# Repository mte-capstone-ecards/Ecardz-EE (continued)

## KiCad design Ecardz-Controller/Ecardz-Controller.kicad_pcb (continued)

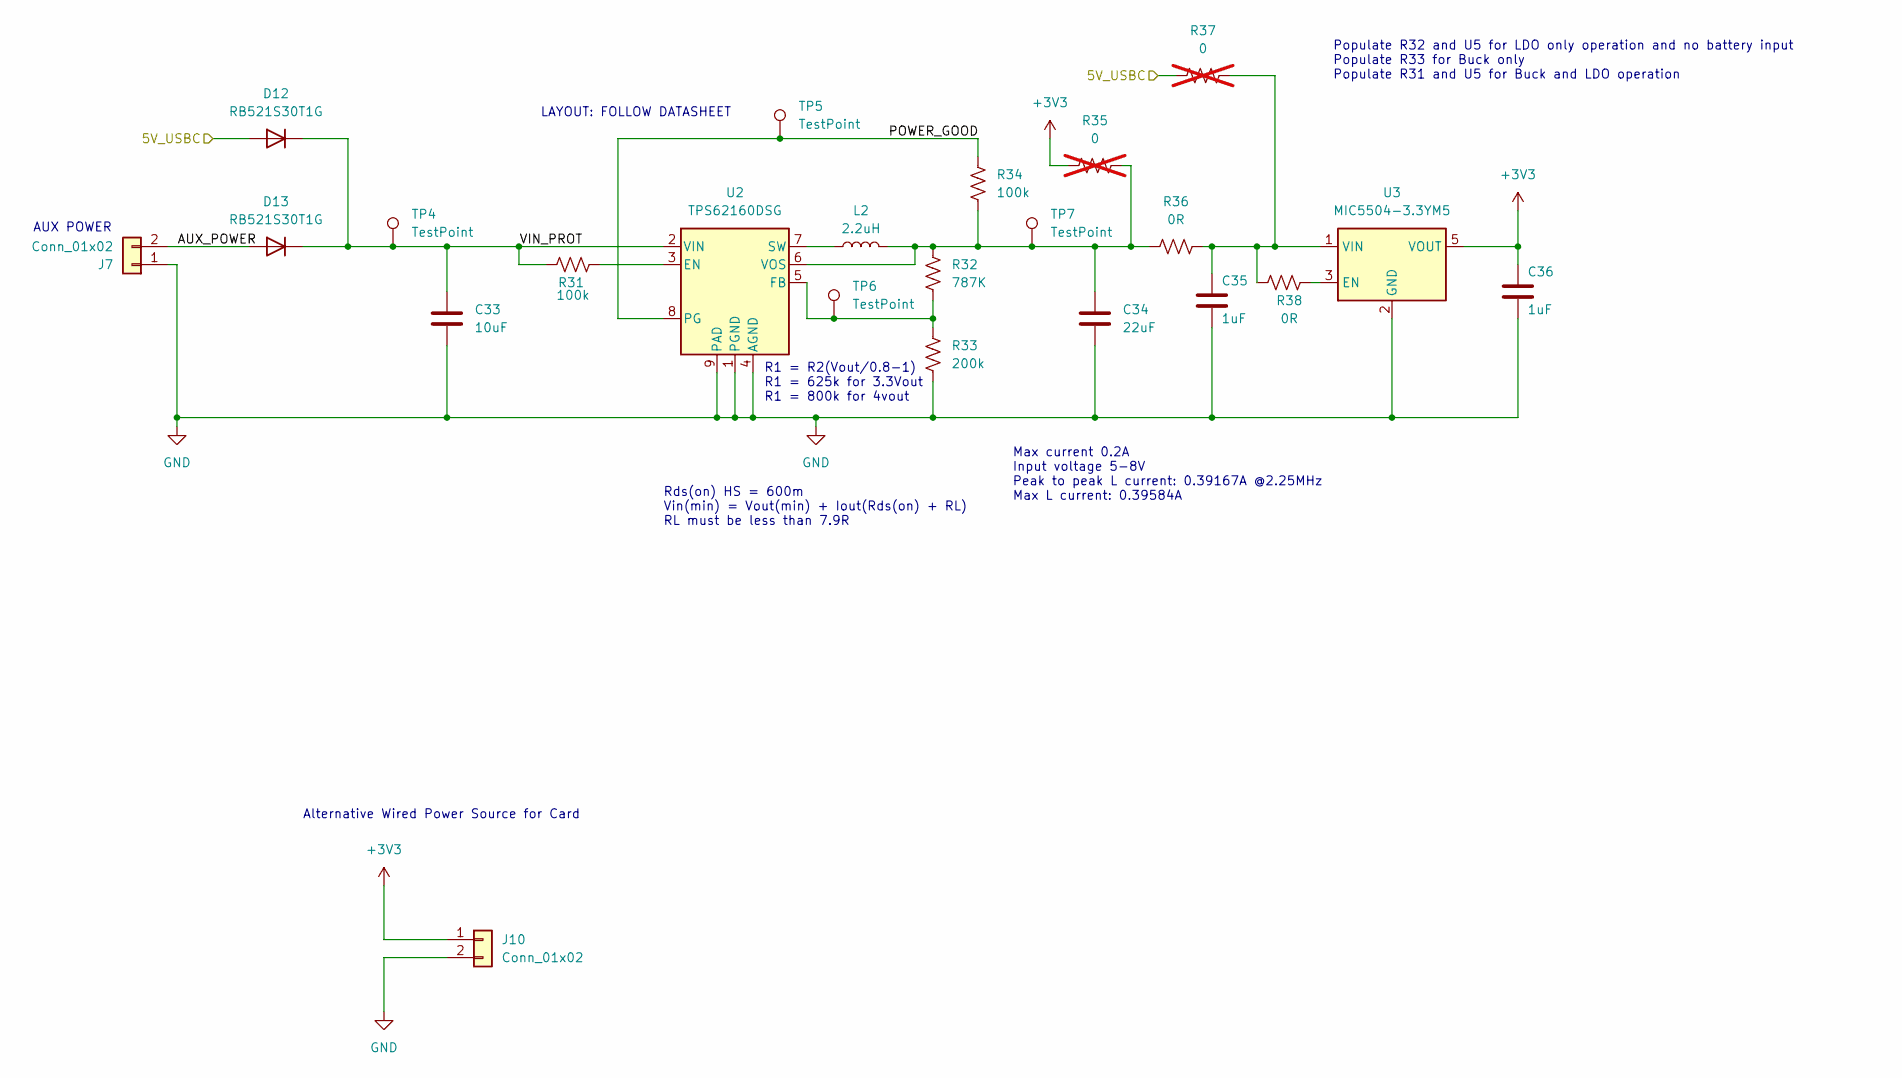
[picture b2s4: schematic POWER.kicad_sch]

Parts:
C33: 10uF; C_0805_2012Metric_Pad1.18x1.45mm_HandSolder; Part Number GRM21BR61C106KE15K
C34: 22uF; C_0805_2012Metric_Pad1.18x1.45mm_HandSolder; Part Number GRM21BR61A226ME51K
C35, C36: 1uF; C_0603_1608Metric_Pad1.08x0.95mm_HandSolder; Part Number CC0603KRX5R8BB105
D12, D13: RB521S30T1G; D_SOD-523; Part Number RB521S30T1G
J7, J10: Conn_01x02; PinHeader_1x02_P2.54mm_Horizontal; Part Number 61300211121
L2: 2.2uH; VLS2016; Part Number VLS201610CX-2R2M-1
R31, R34: 100k; R_0603_1608Metric_Pad0.98x0.95mm_HandSolder; Part Number RC0603FR-07100KL
R32: 787K; R_0603_1608Metric_Pad0.98x0.95mm_HandSolder; Part Number ERJ-3EKF7873V
R33: 200k; R_0603_1608Metric_Pad0.98x0.95mm_HandSolder; Part Number RC0603JR-07200KL
R35, R37: 0; R_0603_1608Metric_Pad0.98x0.95mm_HandSolder; MANUFACTURER PART NUMBER RC0603JR-070RL; Digikey Part Number 311-0.0GRTR-ND; not fitted
R36, R38: 0R; R_0603_1608Metric_Pad0.98x0.95mm_HandSolder; MANUFACTURER PART NUMBER RC0603JR-070RL; Digikey Part Number 311-0.0GRTR-ND
TP4, TP5, TP6, TP7: TestPoint; TestPoint_Pad_D3.0mm
U2: TPS62160DSG; WSON-8-1EP_2x2mm_P0.5mm_EP0.9x1.6mm_ThermalVias; Part Number TPS62160DSG
U3: MIC5504-3.3YM5; SOT-23-5; Part Number MIC5504-3.3YM5-TR

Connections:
+3V3: C36.1, J10.1, R35.1, U3.5 (VOUT); also elsewhere on the board
/POWER/5V_USBC: D12.2 (A), R37.1; also elsewhere on the board
/POWER/AUX_POWER: D13.2 (A), J7.2
/POWER/POWER_GOOD: R34.1, TP5.1, U2.8 (PG)
/POWER/VIN_PROT: C33.1, D12.1 (K), D13.1 (K), R31.2, TP4.1, U2.2 (VIN)
GND: C33.2, C34.2, C35.2, C36.2, J7.1, J10.2, R33.2, U2.1 (PGND), U2.4 (AGND), U2.9 (PAD), U3.2 (GND); also elsewhere on the board
unnamed: R31.1, U2.3 (EN)
unnamed: R32.2, R33.1, TP6.1, U2.5 (FB)
unnamed: L2.1, U2.7 (SW)
unnamed: C34.1, L2.2, R32.1, R34.2, R35.2, R36.1, TP7.1, U2.6 (VOS)
unnamed: R38.1, U3.3 (EN)
unnamed: C35.1, R36.2, R37.2, R38.2, U3.1 (VIN)

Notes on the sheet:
Populate R32 and U5 for LDO only operation and no battery input Populate R33 for Buck only Populate R31 and U5 for Buck and LDO operation
Alternative Wired Power Source for Card
AUX POWER
R1 = R2(Vout/0.8-1) R1 = 625k for 3.3Vout R1 = 800k for 4vout
LAYOUT: FOLLOW DATASHEET
Max current 0.2A Input voltage 5-8V Peak to peak L current: 0.39167A @2.25MHz Max L current: 0.39584A
Rds(on) HS = 600m Vin(min) = Vout(min) + Iout(Rds(on) + RL) RL must be less than 7.9R

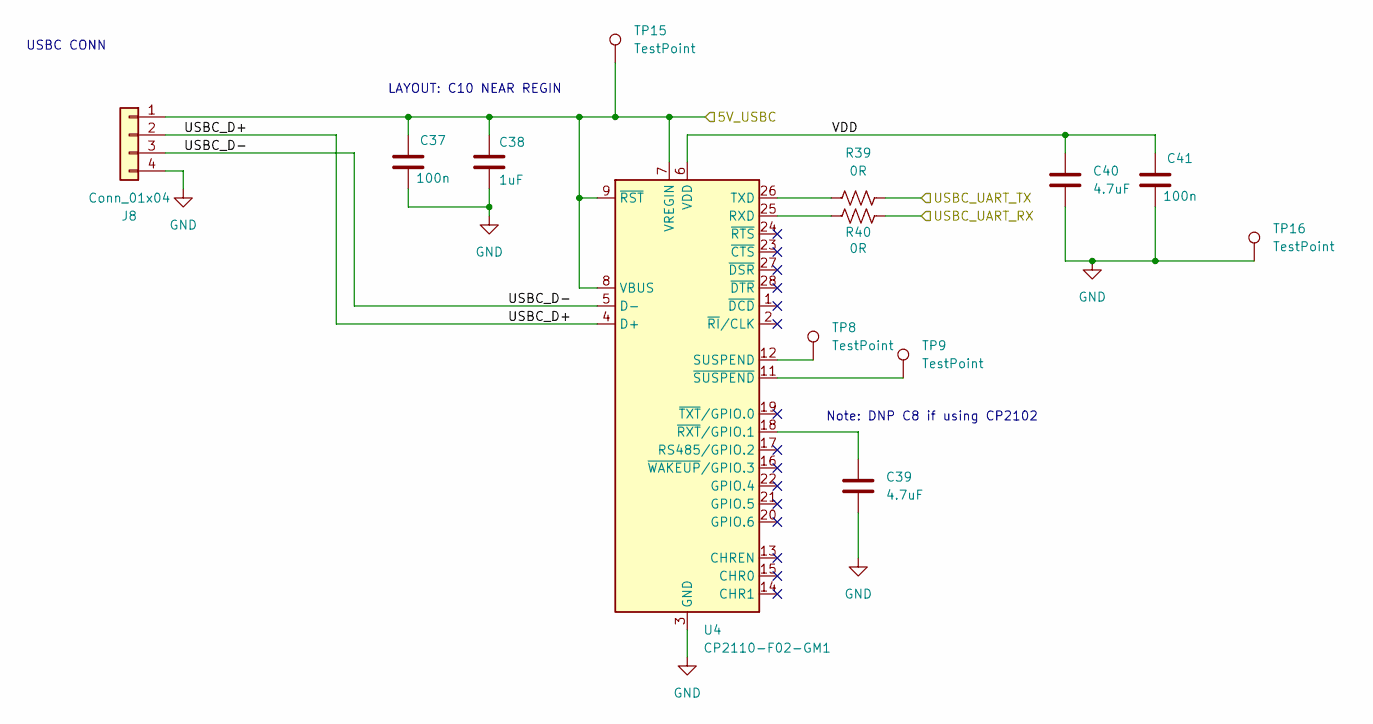
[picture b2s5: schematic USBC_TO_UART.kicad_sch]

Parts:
C37, C41: 100n; C_0603_1608Metric_Pad1.08x0.95mm_HandSolder; Part Number CC0603KRX7R7BB104
C38: 1uF; C_0603_1608Metric_Pad1.08x0.95mm_HandSolder; Part Number CC0603KRX5R8BB105
C39, C40: 4.7uF; C_0603_1608Metric_Pad1.08x0.95mm_HandSolder; Part Number CL10A475KP8NNNC
J8: Conn_01x04; PinHeader_1x04_P2.54mm_Horizontal; Part Number 61300411121
R39, R40: 0R; R_0603_1608Metric_Pad0.98x0.95mm_HandSolder; MANUFACTURER PART NUMBER RC0603JR-070RL; Digikey Part Number 311-0.0GRTR-ND
TP8, TP9, TP15, TP16: TestPoint; TestPoint_Pad_D3.0mm
U4: CP2110-F02-GM1; QFN-28-1EP_5x5mm_P0.5mm_EP3.35x3.35mm; Part Number CP2110-F02-GM1

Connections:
/MCU/USBC_UART_RX: R40.2; also elsewhere on the board
/MCU/USBC_UART_TX: R39.2; also elsewhere on the board
/POWER/5V_USBC: C37.1, C38.1, J8.1, TP15.1, U4.7 (VREGIN), U4.8 (VBUS), U4.9 (~RST); also elsewhere on the board
/USBC_TO_UART/USBC_D+: J8.2, U4.4 (D+)
/USBC_TO_UART/USBC_D-: J8.3, U4.5 (D-)
/USBC_TO_UART/VDD: C40.1, C41.1, U4.6 (VDD)
GND: C37.2, C38.2, C39.2, C40.2, C41.2, J8.4, TP16.1, U4.3 (GND), U4.29 (GND); also elsewhere on the board
unnamed: R40.1, U4.25 (RXD)
unnamed: TP8.1, U4.12 (SUSPEND)
unnamed: R39.1, U4.26 (TXD)
unnamed: C39.1, U4.18 (~RXT/GPIO.1)
unnamed: TP9.1, U4.11 (~SUSPEND)

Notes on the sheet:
USBC CONN
Note: DNP C8 if using CP2102
LAYOUT: C10 NEAR REGIN

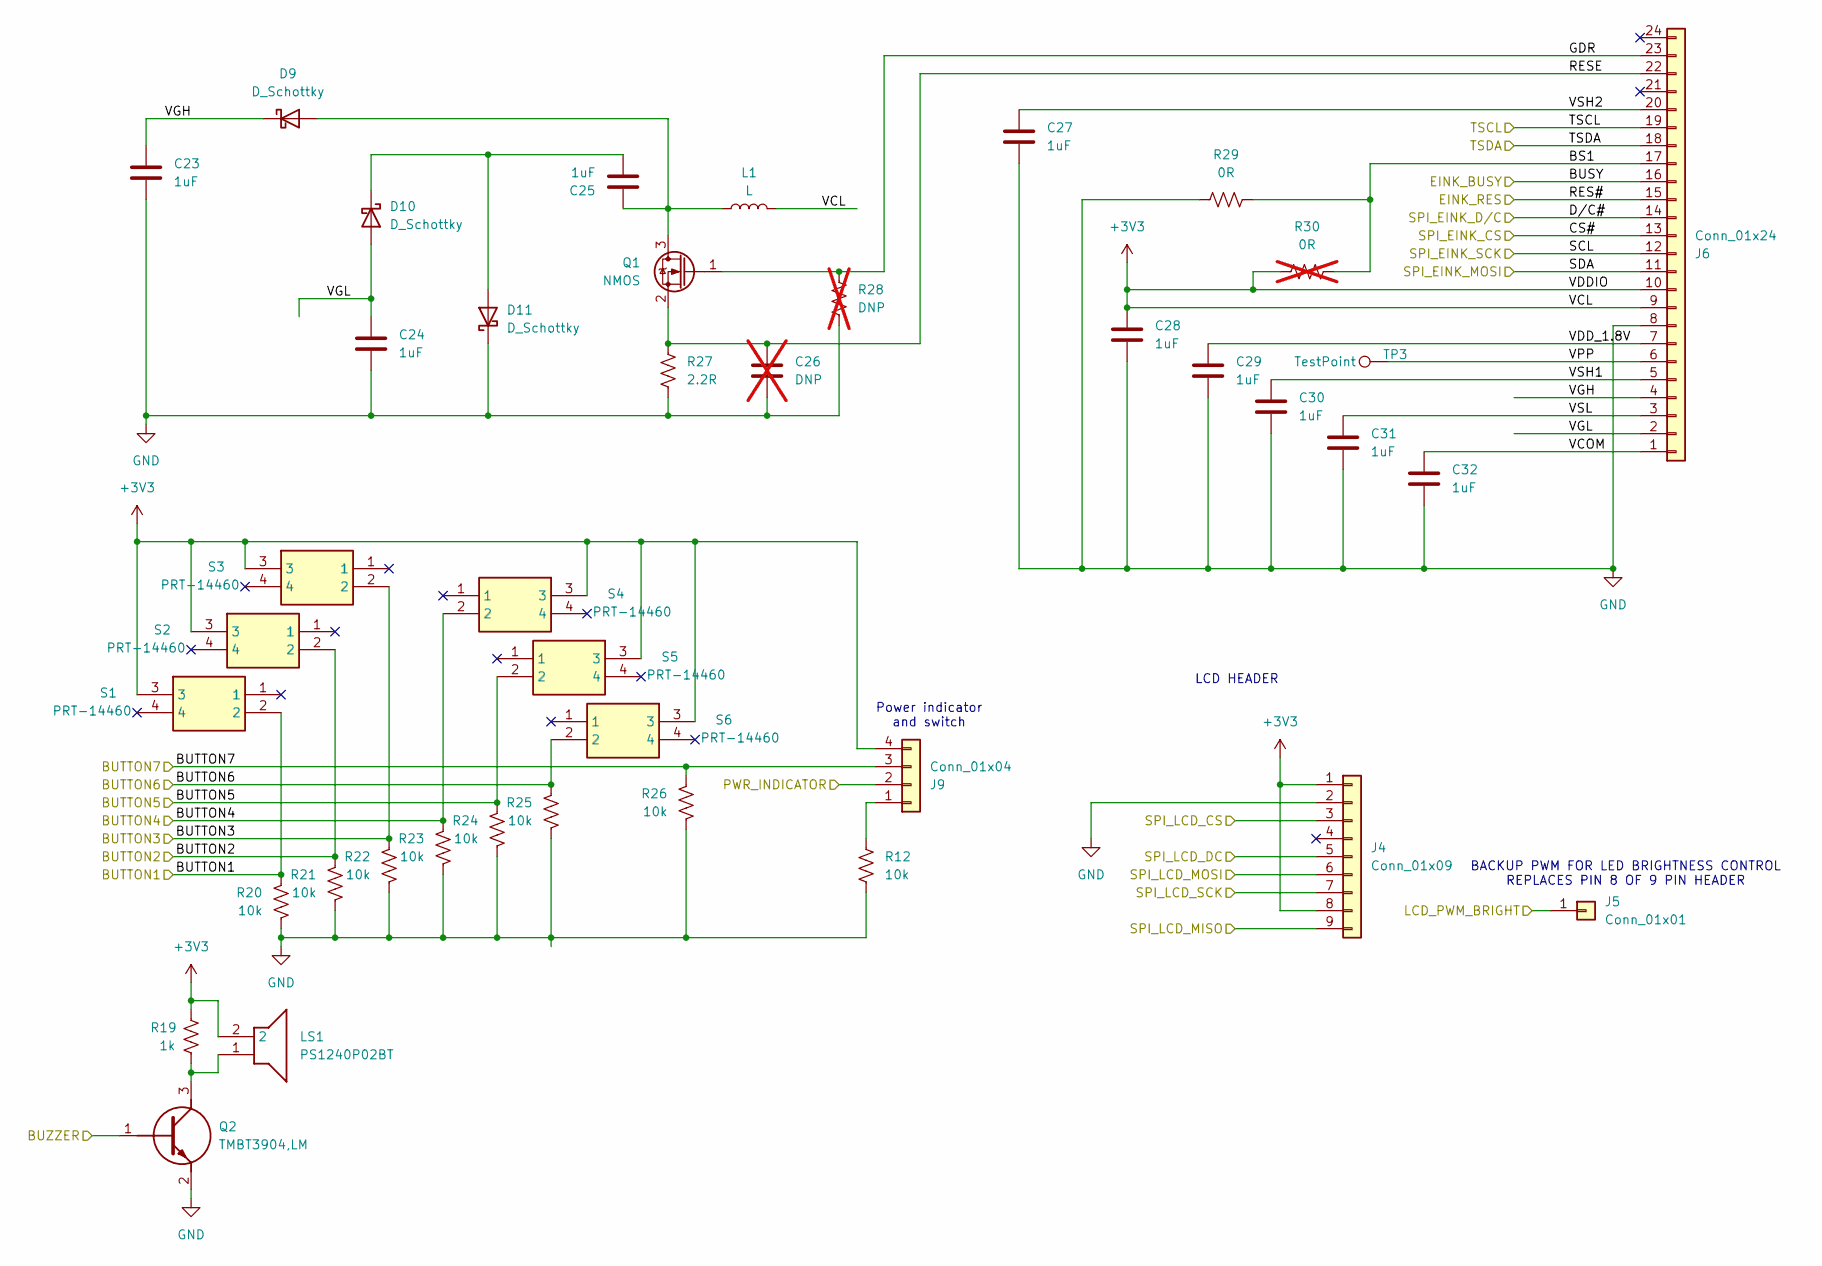
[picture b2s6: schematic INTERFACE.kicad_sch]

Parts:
C23, C24, C25, C27, C28, C29, C30, C31, C32: 1uF; C_0603_1608Metric_Pad1.08x0.95mm_HandSolder; MANUFACTURER PART NUMBER CC0603KRX5R8BB105; Digikey Part Number 311-1445-2-ND
C26: DNP; C_0603_1608Metric_Pad1.08x0.95mm_HandSolder; MANUFACTURER PART NUMBER 100pF; not fitted
D9, D10, D11: D_Schottky; D_SOD-123; MANUFACTURER PART NUMBER MBR0530T1G; Digikey Part Number MBR0530T1GOSTR-ND
J4: Conn_01x09; PinHeader_1x09_P2.54mm_Horizontal; Part Number 61300911121
J5: Conn_01x01; PinHeader_1x01_P2.54mm_Horizontal; Part Number 61300111121
J6: Conn_01x24; TE_2-1734839-4_1x24-1MP_P0.5mm_Horizontal; MANUFACTURER PART NUMBER 10051922-2410ELF
J9: Conn_01x04; PinHeader_1x04_P2.54mm_Horizontal; Part Number 61300411121
L1: L; CDRH5D18; MANUFACTURER PART NUMBER CDRH5D18NP-470NC; Digikey Part Number 308-2060-2-ND
LS1: PS1240P02BT; Mouser Part Number 810-PS1240P02BT
Q1: NMOS; SOT-23; MANUFACTURER PART NUMBER IRLML2803TRPBF; Digikey Part Number IRLML2803PBFTR-ND
Q2: TMBT3904,LM; TMBT3904LM; Mouser Part Number 757-TMBT3904LM
R12, R20, R21, R22, R23, R24, R25, R26: 10k; R_0603_1608Metric_Pad0.98x0.95mm_HandSolder; Part Number RC0603FR-0710KL
R19: 1k; R_0603_1608Metric_Pad0.98x0.95mm_HandSolder; Part Number RC0603FR-071KL
R27: 2.2R; R_0603_1608Metric_Pad0.98x0.95mm_HandSolder; MANUFACTURER PART NUMBER RC0603FR-072R2L; Digikey Part Number 311-2.2HRTR-ND
R28: DNP; R_0603_1608Metric_Pad0.98x0.95mm_HandSolder; MANUFACTURER PART NUMBER 100kR; not fitted
R29: 0R; R_0603_1608Metric_Pad0.98x0.95mm_HandSolder; MANUFACTURER PART NUMBER RC0603JR-070RL; Digikey Part Number 311-0.0GRTR-ND
R30: 0R; R_0603_1608Metric_Pad0.98x0.95mm_HandSolder; MANUFACTURER PART NUMBER RC0603JR-070RL; Digikey Part Number 311-0.0GRTR-ND; not fitted
S1, S2, S3, S4, S5, S6: PRT-14460; PRT14460; Mouser Part Number 474-PRT-14460
TP3: TestPoint; TestPoint_Pad_D3.0mm

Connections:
+3V3: C28.1, J4.1, J4.8, J6.9, J6.10, J9.4, L1.2, LS1.2, R19.1, R30.1, S1.3, S2.3, S3.3, S4.3, S5.3, S6.3; also elsewhere on the board
/INTERFACE/BS1: J6.17, R29.2, R30.2
/INTERFACE/BUSY: J6.16; also elsewhere on the board
/INTERFACE/BUTTON1: R20.1, S1.2; also elsewhere on the board
/INTERFACE/BUTTON2: R21.1, S2.2; also elsewhere on the board
/INTERFACE/BUTTON3: R22.1, S3.2; also elsewhere on the board
/INTERFACE/BUTTON4: R23.1, S4.2; also elsewhere on the board
/INTERFACE/BUTTON5: R24.1, S5.2; also elsewhere on the board
/INTERFACE/BUTTON6: R25.1, S6.2; also elsewhere on the board
/INTERFACE/BUTTON7: J9.3, R26.1; also elsewhere on the board
/INTERFACE/BUZZER: Q2.1 (B); also elsewhere on the board
/INTERFACE/CS#: J6.13; also elsewhere on the board
/INTERFACE/D/C#: J6.14; also elsewhere on the board
/INTERFACE/GDR: J6.23, Q1.1 (G), R28.1
/INTERFACE/LCD_PWM_BRIGHT: J5.1; also elsewhere on the board
/INTERFACE/RES#: J6.15; also elsewhere on the board
/INTERFACE/RESE: C26.1, J6.22, Q1.2 (S), R27.1
/INTERFACE/SCL: J6.12; also elsewhere on the board
/INTERFACE/SDA: J6.11; also elsewhere on the board
/INTERFACE/TSCL: J6.19
/INTERFACE/TSDA: J6.18
/INTERFACE/VCOM: C32.1, J6.1
/INTERFACE/VDD_1.8V: C29.1, J6.7
/INTERFACE/VGH: C23.1, D9.1 (K), J6.4
/INTERFACE/VGL: C24.1, D10.2 (A), J6.2
/INTERFACE/VPP: J6.6, TP3.1
/INTERFACE/VSH1: C30.1, J6.5
/INTERFACE/VSH2: C27.1, J6.20
/INTERFACE/VSL: C31.1, J6.3
/MCU/PWR_INDICATOR: J9.2; also elsewhere on the board
/MCU/SPI_LCD_CS: J4.3; also elsewhere on the board
/MCU/SPI_LCD_DC: J4.5; also elsewhere on the board
/MCU/SPI_LCD_MISO: J4.9; also elsewhere on the board
/MCU/SPI_LCD_MOSI: J4.6; also elsewhere on the board
/MCU/SPI_LCD_SCK: J4.7; also elsewhere on the board
GND: C23.2, C24.2, C26.2, C27.2, C28.2, C29.2, C30.2, C31.2, C32.2, D11.1 (K), J4.2, J6.8, Q2.2 (E), R12.2, R20.2, R21.2, R22.2, R23.2, R24.2, R25.2, R26.2, R27.2, R28.2, R29.1; also elsewhere on the board
unnamed: C25.1, D9.2 (A), L1.1, Q1.3 (D)
unnamed: C25.2, D10.1 (K), D11.2 (A)
unnamed: J9.1, R12.1
unnamed: LS1.1, Q2.3 (C), R19.2

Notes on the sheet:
Power indicator and switch
LCD HEADER
BACKUP PWM FOR LED BRIGHTNESS CONTROL REPLACES PIN 8 OF 9 PIN HEADER

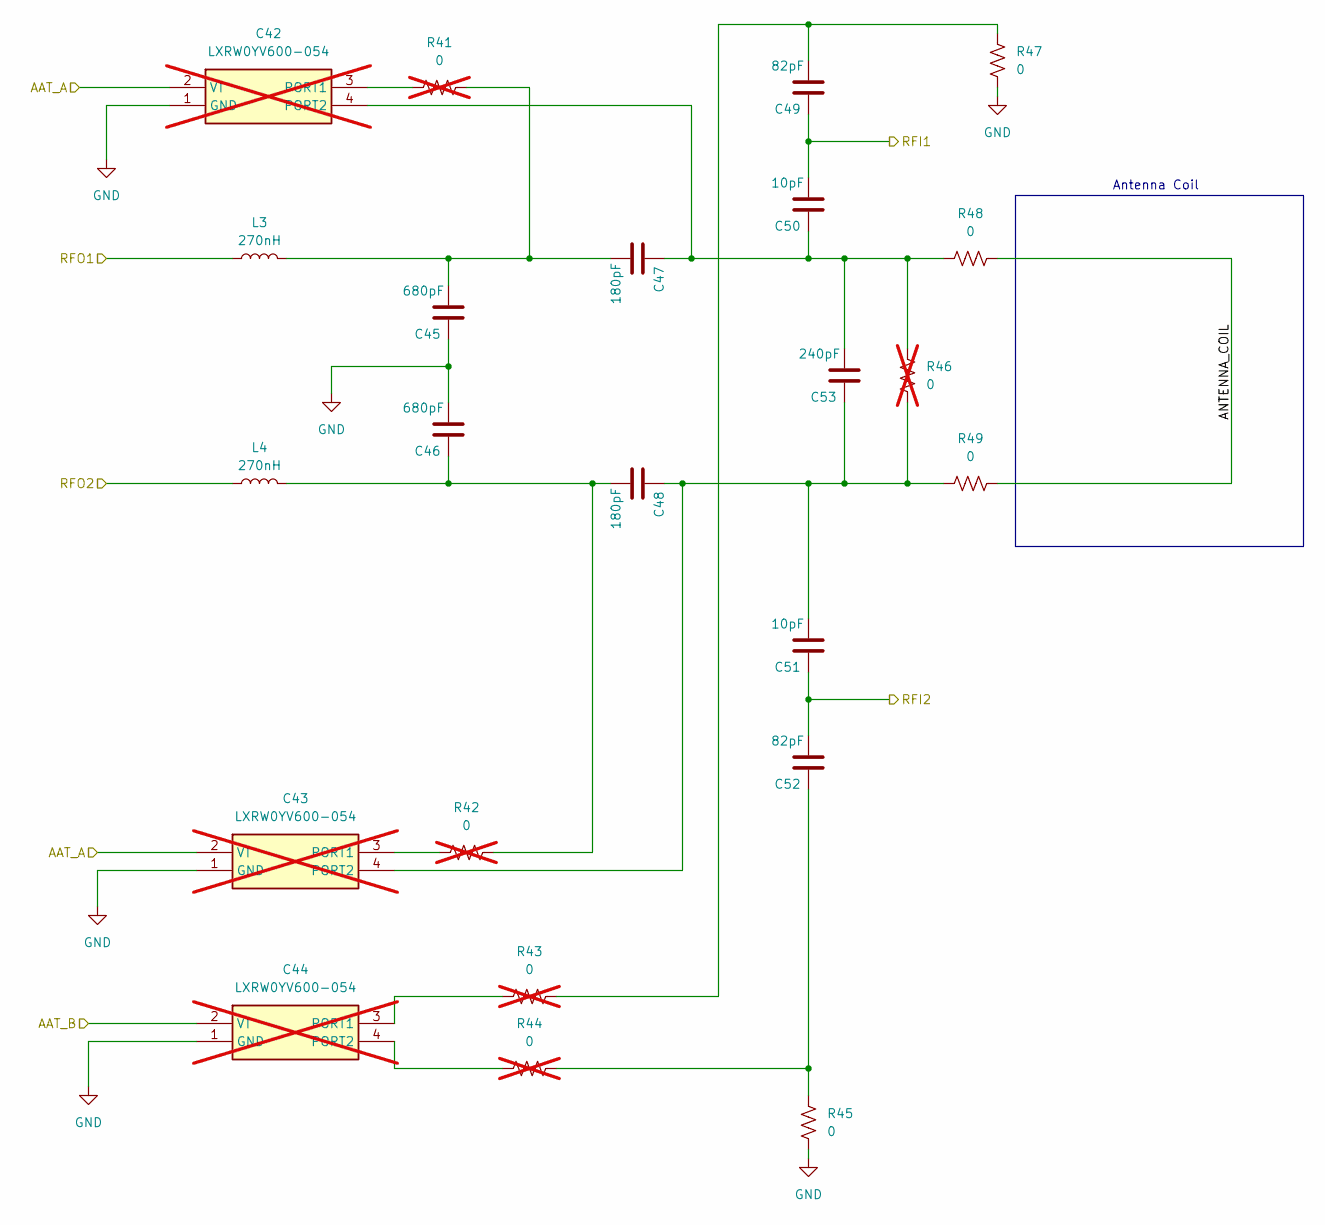
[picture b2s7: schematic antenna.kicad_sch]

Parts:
C42, C43, C44: LXRW0YV600-054; LXRW0YV600054; Mouser Part Number 81-LXRW0YV600-054; not fitted
C45, C46: 680pF; C_0603_1608Metric_Pad1.08x0.95mm_HandSolder; MANUFACTURER PART NUMBER CC0603KRX5R8BB105; Digikey Part Number 311-1445-2-ND
C47, C48: 180pF; C_0603_1608Metric_Pad1.08x0.95mm_HandSolder; MANUFACTURER PART NUMBER CC0603KRX5R8BB105; Digikey Part Number 311-1445-2-ND
C49, C52: 82pF; C_0603_1608Metric_Pad1.08x0.95mm_HandSolder; MANUFACTURER PART NUMBER CC0603KRX5R8BB105; Digikey Part Number 311-1445-2-ND
C50, C51: 10pF; C_0603_1608Metric_Pad1.08x0.95mm_HandSolder; MANUFACTURER PART NUMBER CC0603KRX5R8BB105; Digikey Part Number 311-1445-2-ND
C53: 240pF; C_0603_1608Metric_Pad1.08x0.95mm_HandSolder; MANUFACTURER PART NUMBER CC0603KRX5R8BB105; Digikey Part Number 311-1445-2-ND
L3, L4: 270nH; L_0603_1608Metric; MANUFACTURER PART NUMBER CDRH5D18NP-470NC; Digikey Part Number 308-2060-2-ND
R41, R42, R43, R44, R46: 0; R_0603_1608Metric_Pad0.98x0.95mm_HandSolder; MANUFACTURER PART NUMBER CRCW0603590RFKEA; Digikey Part Number 541-590HTR-ND; not fitted
R45, R47, R48, R49: 0; R_0603_1608Metric_Pad0.98x0.95mm_HandSolder; MANUFACTURER PART NUMBER CRCW0603590RFKEA; Digikey Part Number 541-590HTR-ND

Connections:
/NFC/ANTENNA/AAT_A: C42.2 (VT), C43.2 (VT); also elsewhere on the board
/NFC/ANTENNA/AAT_B: C44.2 (VT); also elsewhere on the board
/NFC/ANTENNA/ANTENNA_COIL: R48.2, R49.2
/NFC/ANTENNA/RFI1: C49.1, C50.2; also elsewhere on the board
/NFC/ANTENNA/RFI2: C51.1, C52.2; also elsewhere on the board
/NFC/ANTENNA/RFO1: L3.1; also elsewhere on the board
/NFC/ANTENNA/RFO2: L4.1; also elsewhere on the board
GND: C42.1 (GND), C43.1 (GND), C44.1 (GND), C45.1, C46.2, R45.2, R47.2; also elsewhere on the board
unnamed: C42.3 (PORT1), R41.1
unnamed: C42.4 (PORT2), C47.1, C50.1, C53.2, R46.2, R48.1
unnamed: C43.3 (PORT1), R42.1
unnamed: C43.4 (PORT2), C48.1, C51.2, C53.1, R46.1, R49.1
unnamed: C44.3 (PORT1), R43.1
unnamed: C44.4 (PORT2), R44.1
unnamed: C45.2, C47.2, L3.2, R41.2
unnamed: C46.1, C48.2, L4.2, R42.2
unnamed: C49.2, R43.2, R47.1
unnamed: C52.1, R44.2, R45.1

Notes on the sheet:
Antenna Coil

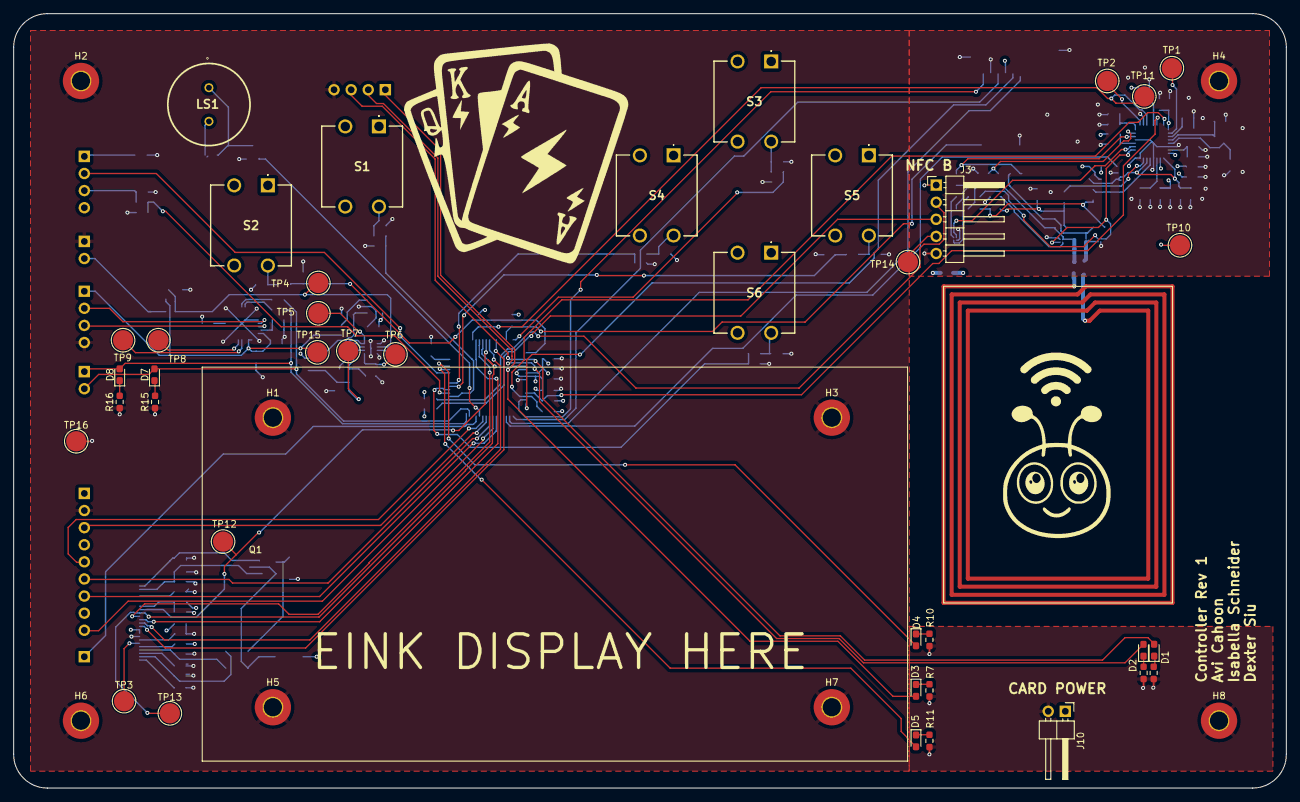
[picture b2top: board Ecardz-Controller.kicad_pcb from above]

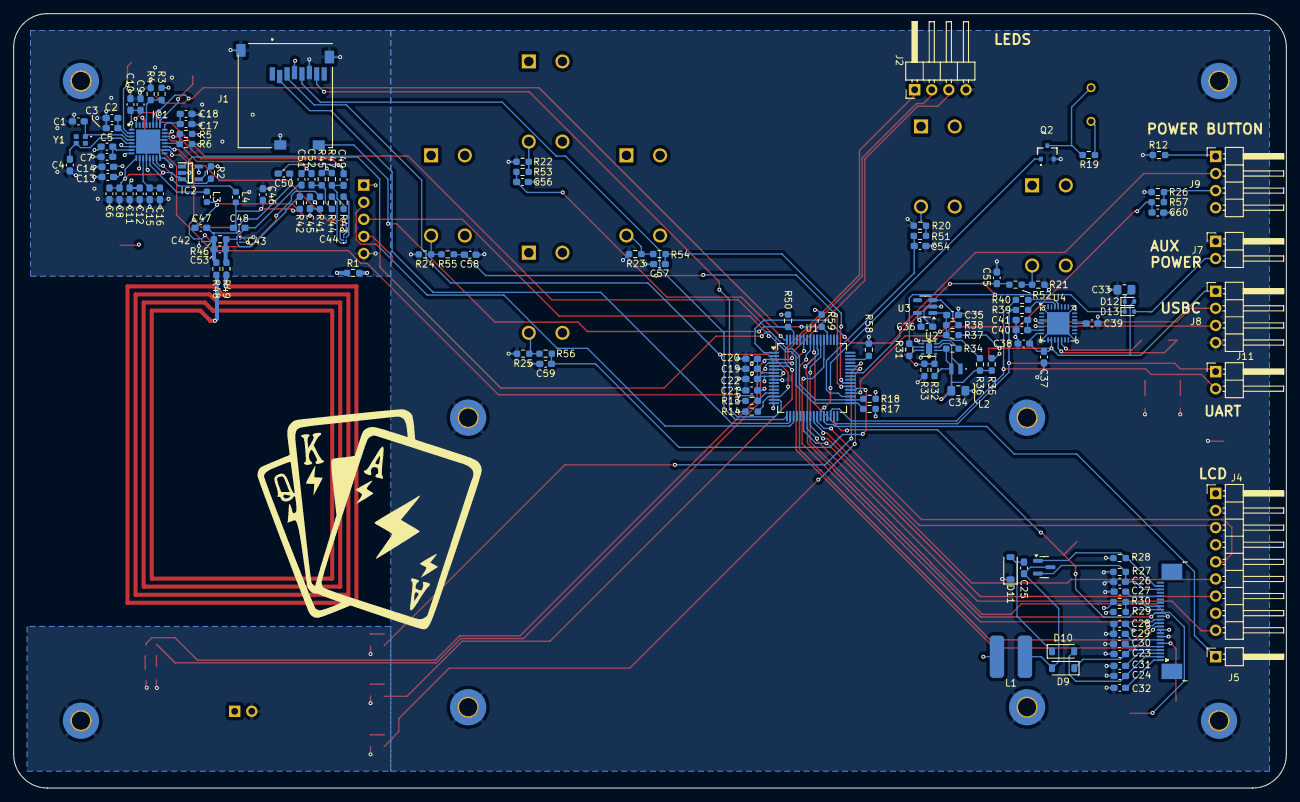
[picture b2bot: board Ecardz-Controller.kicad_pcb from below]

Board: 4 copper layers, 189.0 x 115.0 mm, 186 parts (139 on the bottom side), 119 nets.

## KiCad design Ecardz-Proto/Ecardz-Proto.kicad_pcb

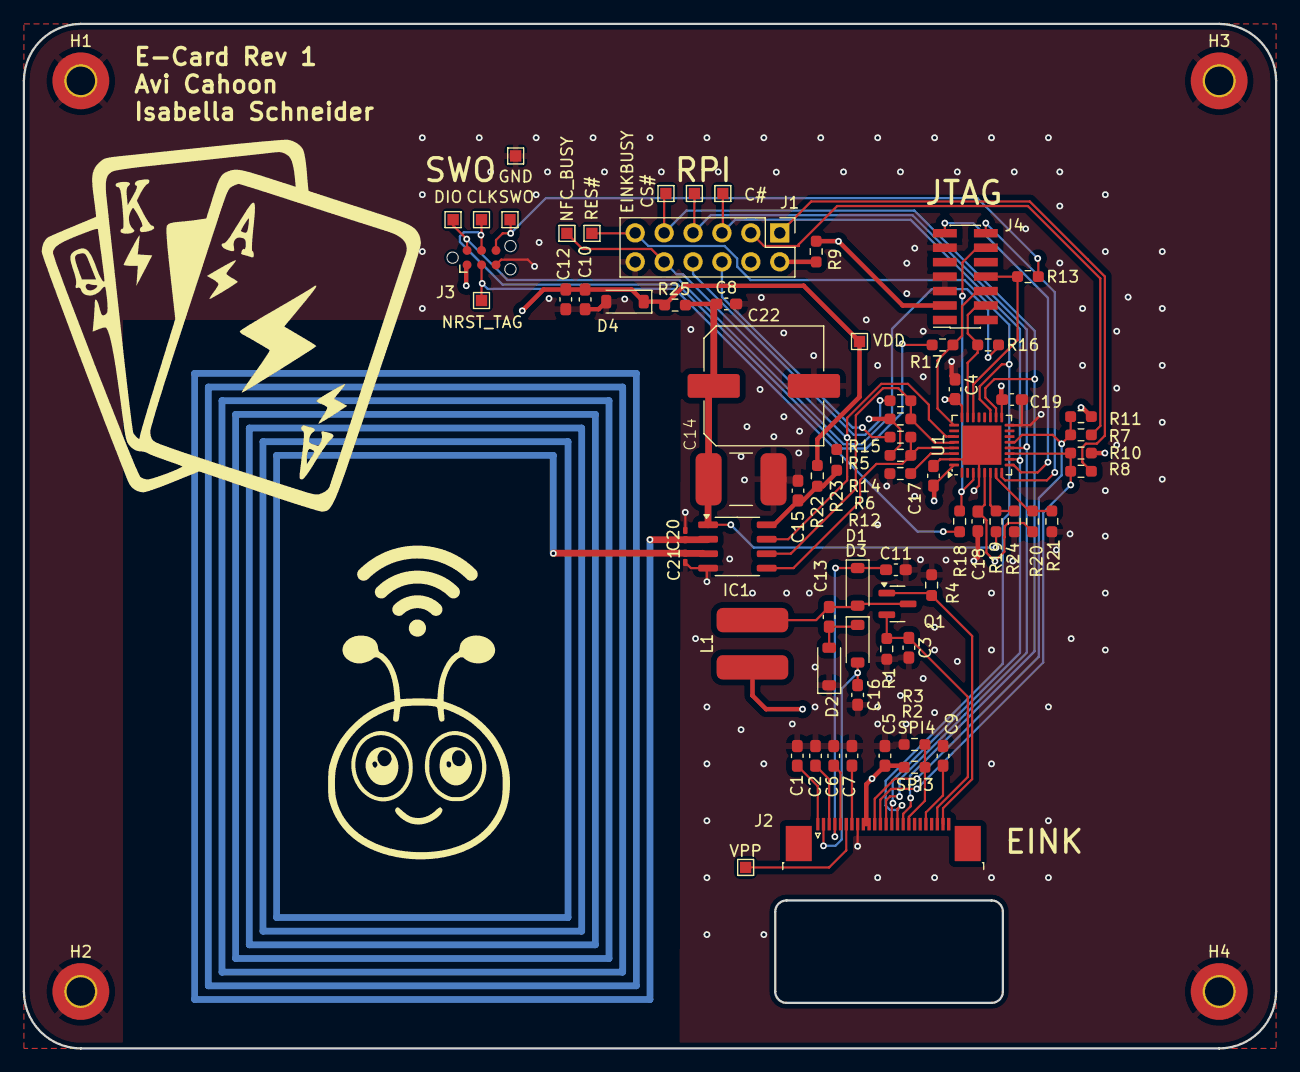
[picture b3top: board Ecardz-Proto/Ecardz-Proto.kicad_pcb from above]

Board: 4 copper layers, 110.0 x 90.0 mm, 75 parts (0 on the bottom side), 45 nets.

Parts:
C1, C2, C4, C5, C6, C7, C9, C11, C13, C16, C17, C18, C19: 1uF; C_0603_1608Metric_Pad1.08x0.95mm_HandSolder
C3: DNP; C_0603_1608Metric_Pad1.08x0.95mm_HandSolder
C8, C10, C12: TBD; C_0603_1608Metric_Pad1.08x0.95mm_HandSolder
C14: TBD; C_2917
C15: 10nF; C_0603_1608Metric_Pad1.08x0.95mm_HandSolder
C20, C21: 7pF; C_0201_0603Metric_Pad0.64x0.40mm_HandSolder
C22: TBD; C_Elec_10x10.2
C#: TestPoint; TestPoint_Pad_1.0x1.0mm
CLK: TestPoint; TestPoint_Pad_1.0x1.0mm
CS#: TestPoint; TestPoint_Pad_1.0x1.0mm
D1, D2, D3: D_Schottky; D_SOD-123
D4: D_Zener; D_SOD-123
DIO: TestPoint; TestPoint_Pad_1.0x1.0mm
EINKBUSY: TestPoint; TestPoint_Pad_1.0x1.0mm
GND: TestPoint; TestPoint_Pad_1.0x1.0mm
H1, H2, H3, H4: MountingHole_Pad; MountingHole_2.5mm_Pad_TopBottom
IC1: M24LR04E-RMN6T/2; SO-8_3.9x4.9mm_P1.27mm
J1: Conn_02x06_Odd_Even; PinHeader_2x06_P2.54mm_Vertical
J2: Conn_01x24; TE_2-1734839-4_1x24-1MP_P0.5mm_Horizontal
J3: Conn_ARM_SWD_TagConnect_TC2030-NL; Tag-Connect_TC2030-IDC-NL_2x03_P1.27mm_Vertical
J4: Conn_02x07_Odd_Even; PinSocket_2x07_P1.27mm_Vertical_SMD
L1: L; CDRH5D18
NFC_BUSY: TestPoint; TestPoint_Pad_1.0x1.0mm
NRST_TAG: TestPoint; TestPoint_Pad_1.0x1.0mm
Q1: NMOS; SOT-23
R1: 2.2R; R_0603_1608Metric_Pad0.98x0.95mm_HandSolder
R2, R3: 0R; R_0603_1608Metric_Pad0.98x0.95mm_HandSolder
R4, R5, R6, R7, R8, R9, R10, R11, R12, R13, R14, R15, R16, R17, R18, R22, R23: DNP; R_0603_1608Metric_Pad0.98x0.95mm_HandSolder
R19, R20, R21, R24: 10k; R_0603_1608Metric_Pad0.98x0.95mm_HandSolder
R25: 600R; R_0603_1608Metric_Pad0.98x0.95mm_HandSolder
RES#: TestPoint; TestPoint_Pad_1.0x1.0mm
SWO: TestPoint; TestPoint_Pad_1.0x1.0mm
U1: STM32L071K8Ux; QFN-32-1EP_5x5mm_P0.5mm_EP3.45x3.45mm
VDD: TestPoint; TestPoint_Pad_1.0x1.0mm
VPP: TestPoint; TestPoint_Pad_1.0x1.0mm

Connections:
+3.3V: J1.2, R9.2
/EINK/BS1: J2.17, R2.2, R3.2
/EINK/BUSY: EINKBUSY.1, J1.9, J2.16, U1.18 (PA8)
/EINK/CS#: CS#.1, J1.7, J2.13, U1.12 (PA6)
/EINK/D/C#: C#.1, J1.5, J2.14, U1.10 (PA4)
/EINK/GDR: J2.23, Q1.1 (G), R4.1
/EINK/RES#: J1.11, J2.15, RES#.1, U1.19 (PA9)
/EINK/RESE: C3.1, J2.22, Q1.2 (S), R1.1
/EINK/SCL: J2.12, R8.2, R10.1, U1.11 (PA5)
/EINK/SDA: J2.11, R7.2, R11.1, U1.13 (PA7)
/EINK/VCOM: C1.1, J2.1
/EINK/VDD_1.8V: C7.1, J2.7
/EINK/VGH: C11.1, D1.1 (K), J2.4
/EINK/VGL: C16.1, D3.2 (A), J2.2
/EINK/VPP: J2.6, VPP.1
/EINK/VSH1: C6.1, J2.5
/EINK/VSH2: C9.1, J2.20
/EINK/VSL: C2.1, J2.3
/NFC/VDD_NFC: C15.1, IC1.8 (VCC), R22.1, R23.1
/NFC/V_E_HARVEST: C8.1, C14.1, C22.1, IC1.1 (VOUT), R19.1, R25.1
/STM/BOOT0: R12.2, U1.30 (BOOT0)
/STM/I2C_NFC_SCL: IC1.6 (SCL), R5.2, R15.2, U1.28 (PB6)
/STM/I2C_NFC_SCL_RPI: J1.8, R15.1
/STM/I2C_NFC_SDA: IC1.5 (SDA), R6.2, R14.2, U1.29 (PB7)
/STM/I2C_NFC_SDA_RPI: J1.6, R14.1
/STM/NFC_BUSY: IC1.7 (RF_WIP/BUSY), J1.10, NFC_BUSY.1, U1.27 (PB5)
/STM/NRST: J4.12, R18.2, U1.3 (NRST)
/STM/NRST_TAG: J3.3 (~RESET), NRST_TAG.1, R18.1
/STM/SPI_EINK_SCL_RPI: J1.1, R10.2
/STM/SPI_EINK_SDA_RPI: J1.3, R11.2
/STM/SWCLK: J4.6, R17.1, U1.25 (PA14)
/STM/SWCLK_TAG: CLK.1, J3.4 (SWCLK), R17.2
/STM/SWDIO: J4.4, R16.1, U1.23 (PA13)
/STM/SWDIO_TAG: DIO.1, J3.2 (SWDIO), R16.2
/STM/SWO: J4.8, R13.1, U1.22 (PA12)
/STM/SWO_TAG: J3.6 (SWO), R13.2, SWO.1
/STM/T_VCP_RX: J4.13, U1.9 (PA3)
/STM/T_VCP_TX: J4.14, U1.8 (PA2)
/STM/VDD_MEAS: R20.2, R21.1, U1.7 (PA1)
GND: C1.2, C2.2, C3.2, C4.1, C5.2, C6.2, C7.2, C8.2, C9.2, C10.2, C11.2, C12.2, C14.2, C15.2, C16.2, C17.1, C18.1, C19.1, C20.2, C21.2, C22.2, D2.1 (K), D4.2 (A), GND.1, H1.1, H2.1, H3.1, H4.1, IC1.4 (VSS), J1.12, J2.8, J3.5 (GND), J4.5, J4.7, J4.11, R1.2, R3.1, R4.2, R12.1, R21.2, R24.2, U1.4 (VSSA), U1.16 (VSS), U1.31 (VSS), U1.33 (VSS)
unnamed: C13.1, D1.2 (A), L1.1, Q1.3 (D)
unnamed: C13.2, D2.2 (A), D3.1 (K)
unnamed: C20.1, C21.1, IC1.2 (AC0), IC1.3 (AC1)
unnamed: R19.2, R24.1, U1.6 (PA0)
VDD: C4.2, C5.1, C10.1, C12.1, C17.2, C18.2, C19.2, D4.1 (K), J2.9, J2.10, J3.1 (VCC), J4.3, L1.2, R2.1, R5.1, R6.1, R7.1, R8.1, R9.1, R20.1, R22.2, R25.2, U1.5 (VDDA), U1.17 (VDD), U1.24 (VDDIO2), U1.32 (VDD), VDD.1

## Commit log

2024-05-08 new project doc
2024-05-08 just kidding we gonna use kicad
2024-06-27 New kicad project
    added kicad project and EINK interface
2024-10-07 added submodule for parts library
2024-10-07 updated parts-lib to newer update
2024-10-07 added EEPROM schematic, removed personal files
2024-10-26 Update .gitmodules
    trying to make it use ssh instead of https
2024-10-26 added energy harvesting schematic page
2024-10-26 upated E-ink schematic
    should be done - just missing inductor footprint
2024-10-29 added energy harvesting sensing ADC to NFC
2024-10-29 updated submodule
2024-11-04 removed eeprom
2024-11-06 added STM and rpi pin connections.
2024-11-09 updated STM pinout
    Updated RPI to just be breakout headers
    Added JTAG connector and LPUSART
    Updated to final? STM pinout
2024-11-09 added VDD cap
2024-11-09 made all supply voltages VDD rather than mix of VDD/VCC, added VDD measurement via STM32 internal ADC, put DNP jumper for VPP on E-ink connector, and made NFC VCC pin only connected to power if exter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
2024-11-09 added jumpers to select NFC chip's power supply connection
2024-11-10 updated most footprints
2024-11-10 board outline
2024-11-10 added a C_2917 cap to NFC energy harvesting in case needed
2024-11-10 added antenna tuning caps
2024-11-10 rough layout complete
    need to fix silkscreens and finish antenna
2024-11-11 fit layout in 4.2in card size
2024-11-11 added more space around antenna
2024-11-11 added large cap to layout
2024-11-12 added zener and extra cap footprints
2024-11-12 updated inductor
2024-11-12 updated silkscreen
2024-11-12 silkscreen images
    and fixed layout DRCs
2024-11-13 gerbers generated for first fab
2024-11-13 added stitching vias
2024-11-13 final gerbers for first fab
2024-11-15 added parts numbers for everything
2024-11-20 new controller schematic
2024-12-19 added buck converter
    just missing inductor part selection
2024-12-22 adding MCU
    added peripheral connections as well as indicator lights
2024-12-22 updated button pin choices, updated root
2025-01-06 usb to uart chip
    currently using the wrong kicad part number but they are footprint compatible
2025-01-06 small updates
    added 0 ohm on uart, more caps on power pins
2025-01-06 added eink and lcd pinouts
2025-01-06 updated parts-lib reference
2025-01-06 added buzzer
2025-01-06 parts-lib update
2025-01-06 finished buzzer and button connections
2025-01-06 added NFC schematic
2025-01-06 added SD card connector into parts-lib
2025-01-06 added inductor to parts lib
2025-01-06 added LDO on buck output and SD card footprint
2025-01-06 fixed FPC connector
2025-01-07 added DXF for mechanical
2025-01-07 updated for dxf
2025-01-07 new card files
2025-01-07 Started board layout + antenna
2025-01-07 Added gitignore
2025-01-07 Edited readme
2025-01-07 initial work on controller layout
2025-01-09 did bulk of controller layout apart from the antenna, added some NCs and other minor clean ups on schematic
2025-01-10 most of layout complete
    switched ADC pins for ease of layout. added LEDs
2025-01-10 removed RPI header
2025-01-10 controller updates
2025-01-13 Added traces for everything but gruond layer
2025-01-13 updates based on review
2025-01-13 Finished layout and silkscreen, need to fix library for inductor and cap
2025-01-13 Finished all layout, need to fix inductor and capacitor library
2025-01-14 added current sense resistor and modified buzzer circuit
2025-01-16 redid MCU connections from IOC file from FW team
2025-01-16 updated layout for new mcu pin assignments
2025-01-16 slightly adjusted LED position
2025-01-16 flipped SD card so it enters from card edge
2025-01-16 changed headers to 90 degree angled headers
2025-01-17 moved headers to bottom of board, made J3 DNP
2025-01-19 changed hole positions and fixed flex connector location in 3d model
2025-01-19 placed button debouncing filter components in layout
2025-01-20 final layout before fab
2025-01-20 Generated gerbers
2025-01-20 turned flex connector around
2025-01-20 new gerbers with rotated FPC connector
2025-02-17 updated parts-lib to add supercaps
2025-02-18 final schematic
    final schematic done and BOM generated except for pogo pins and capacitors
2025-02-22 initial fit check for mech
    final footprints defined and placement is mostly complete
2025-02-22 added antenna jumpers
2025-02-23 second mech spin
2025-02-23 all tracks connected
2025-02-23 final silkscreens
    also made more space around antenna
2025-02-24 final fit check complete.
    added updated step, wrl, gerbers and svg file used for silkscreen
2025-02-24 final final mech spin
2025-03-11 Commented on hanabi
2025-03-12 updated some hanabi TODOS
